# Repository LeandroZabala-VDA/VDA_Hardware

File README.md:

# VDA_Hardware

This repository contains the hardware design files for the **VDA Signal Acquisition System**, a device developed for the non-invasive measurement of **Arterial Diameter Variation (VDA)** using piezoelectric transducers. The system is intended for biomedical research applications and has been validated in both laboratory and clinical environments.

## 📁 Repository Structure

- **/Adquisidor**  
  Contains all design files for the main acquisition board, including schematics, PCB layout, and bill of materials. This board handles signal conditioning, high-resolution analog-to-digital conversion, power regulation, and communication with the PC interface.

- **/frente del gabinete**  
  Includes the PCB designs used as front and rear panels for the device enclosure. These boards support mechanical mounting of connectors, status indicators, and user controls.

## 🛠️ Tools and Compatibility

- Designed using **Autodesk Eagle**  
- Compatible with Eagle version 9.6.2 or later

## ✅ Hardware Status

The version published here is fully functional and has been used in real experimental protocols and patient measurements. It is part of a broader open-source platform that includes firmware and a Python-based user interface.

Key features include:
- Support for a 27 mm piezoelectric transducer
- Fully differential charge amplifier
- Analog bandwidth: 0.16 Hz – 34 Hz
- 16-bit sigma-delta ADC
- 50 Hz digital notch filter
- Electrically isolated sensor interface

## 📂 Included Files

- `.sch` and `.brd` files (schematics and board layout)
- Bill of Materials (`.xls` / `.csv`)
- Reference images of the PCB and assembly
- Enclosure drawings or panel layouts (`.png`, `.step`, etc.)

## 📷 Preview

## 🧩 Related Work

This hardware was developed as part of a final project at the **Laboratorio de Bioingeniería (LABI)**, Universidad Nacional de Mar del Plata (Argentina), and was used in the context of scientific publications, including a peer-reviewed IEEE article.

## 🛡 License

All hardware design files in this repository are licensed under the **CERN Open Hardware License v2 - Strongly Reciprocal (CERN-OHL-S)**.

Any derivative work must also remain open and be shared under the same terms. 

## 📬 Contact

For questions, suggestions or collaboration, feel free to open an issue or contact me.

leandrozabala@mdp.edu.ar

---

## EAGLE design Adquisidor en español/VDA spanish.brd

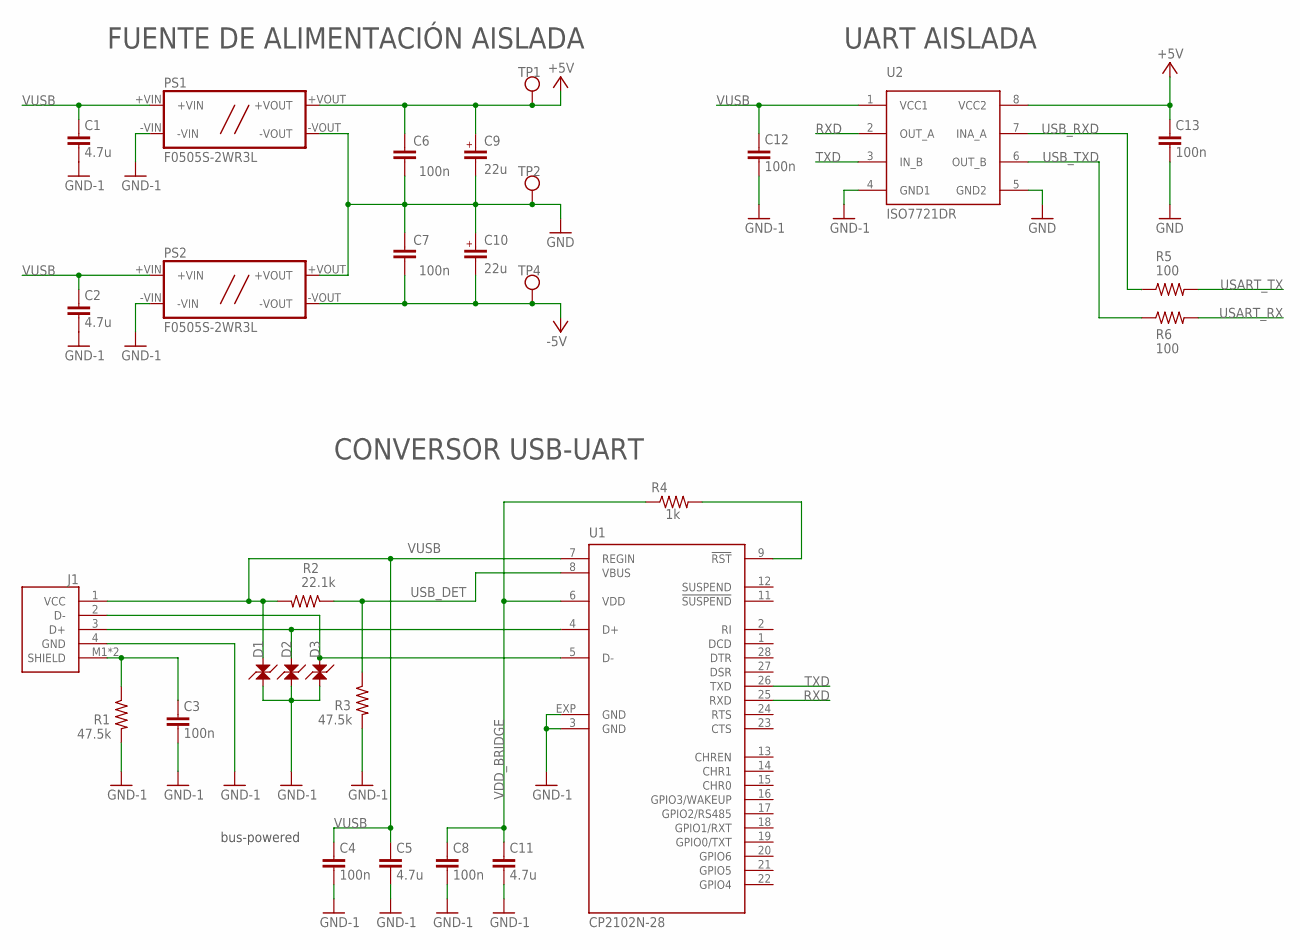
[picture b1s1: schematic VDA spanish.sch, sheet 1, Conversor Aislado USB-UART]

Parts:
C1, C2, C5, C11: 4.7u; C_0805
C3, C4, C6, C7, C8, C12, C13: 100n; C_0603
C9, C10: 22u; CAPAE660X590N
D1, D2, D3: LESD5D5.0CT1G; SOD523
J1: USB-2.0; USB-B
PS1, PS2: F0505S-2WR3L; 0505S-2WR3
R1, R3: 47.5k; R0402
R2: 22.1k; R0402
R4: 1k; R0402
R5, R6: 100; R_0603
TP1, TP2, TP4: HOLE_0.8MM
U1: CP2102N-28; MLP28
U2: ISO7721DR; SO8

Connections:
+5V: C6.P$1 (1), C9.+, C13.P$1 (1), PS1.+VOUT, TP1.1, U2.8 (VCC2); also elsewhere on the board
-5V: C7.P$2 (2), C10.-, PS2.-VOUT, TP4.1; also elsewhere on the board
GND: C6.P$2 (2), C7.P$1 (1), C9.-, C10.+, C13.P$2 (2), PS1.-VOUT, PS2.+VOUT, TP2.1, U2.5 (GND2); also elsewhere on the board
GND-1: C1.P$2 (2), C2.P$2 (2), C3.P$2 (2), C4.P$2 (2), C5.P$2 (2), C8.P$2 (2), C11.P$2 (2), C12.P$2 (2), D1.C, D2.C, D3.C, J1.4 (GND), PS1.-VIN, PS2.-VIN, R1.2, R3.2, U1.3 (GND), U1.EXP (GND), U2.4 (GND1)
unnamed: R4.2, U1.9 (!RST)
RXD: U1.25 (RXD), U2.2 (OUT_A)
SHIELD: C3.P$1 (1), J1.M1 (SHIELD), J1.M2 (SHIELD), R1.1
TXD: U1.26 (TXD), U2.3 (IN_B)
USART_RX: R6.2; also elsewhere on the board
USART_TX: R5.2; also elsewhere on the board
USB_DET: R2.1, R3.1, U1.8 (VBUS)
USB_DN: D3.A, J1.2 (D-), U1.5 (D-)
USB_DP: D2.A, J1.3 (D+), U1.4 (D+)
USB_RXD: R5.1, U2.7 (INA_A)
USB_TXD: R6.1, U2.6 (OUT_B)
VDD_BRIDGE: C8.P$1 (1), C11.P$1 (1), R4.1, U1.6 (VDD)
VUSB: C1.P$1 (1), C2.P$1 (1), C4.P$1 (1), C5.P$1 (1), C12.P$1 (1), D1.A, J1.1 (VCC), PS1.+VIN, PS2.+VIN, R2.2, U1.7 (REGIN), U2.1 (VCC1)

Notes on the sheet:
CONVERSOR USB-UART
bus-powered
FUENTE DE ALIMENTACIÓN AISLADA
UART AISLADA

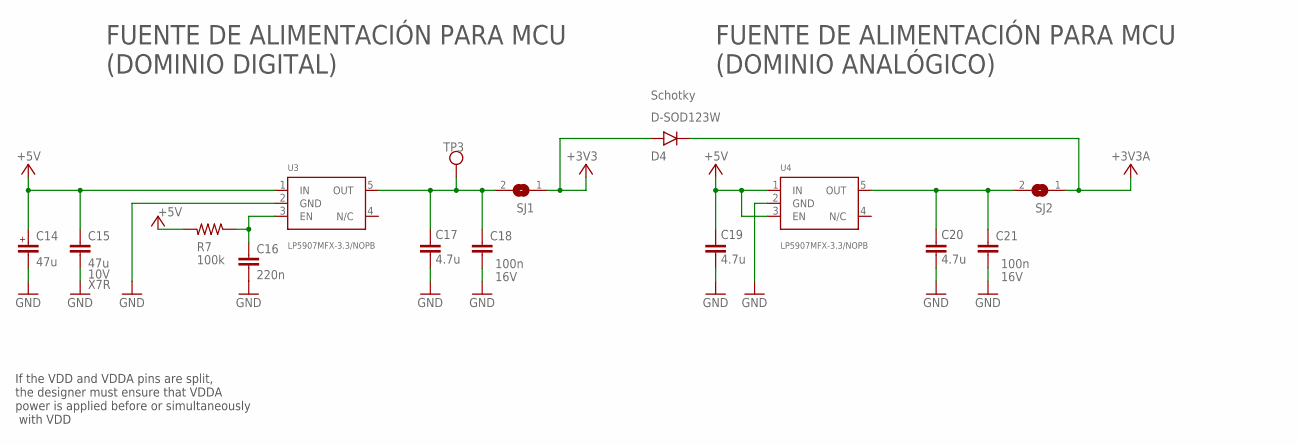
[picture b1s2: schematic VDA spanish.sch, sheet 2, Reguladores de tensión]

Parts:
C14: 47u; A_3216
C15: 47u; C_1206
C16: 220n; C_0603
C17, C19, C20: 4.7u; C_0805
C18, C21: 100n; C_0603
D4: D-SOD123W; SOD123W
R7: 100k; R_0603
SJ1, SJ2: SJ
TP3: HOLE_0.8MM
U3, U4: LP5907MFX-3.3/NOPB; SOT23-5

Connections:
+3V3: D4.A, SJ1.1; also elsewhere on the board
+3V3A: D4.C (K), SJ2.1; also elsewhere on the board
+5V: C14.A (+), C15.P$1 (1), C19.P$1 (1), R7.2, U3.1 (IN), U4.1 (IN), U4.3 (EN); also elsewhere on the board
GND: C14.K (-), C15.P$2 (2), C16.P$2 (2), C17.P$2 (2), C18.P$2 (2), C19.P$2 (2), C20.P$2 (2), C21.P$2 (2), U3.2 (GND), U4.2 (GND); also elsewhere on the board
unnamed: C17.P$1 (1), C18.P$1 (1), SJ1.2, TP3.1, U3.5 (OUT)
unnamed: C16.P$1 (1), R7.1, U3.3 (EN)
unnamed: C20.P$1 (1), C21.P$1 (1), SJ2.2, U4.5 (OUT)

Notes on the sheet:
If the VDD and VDDA pins are split, the designer must ensure that VDDA power is applied before or simultaneously with VDD
FUENTE DE ALIMENTACIÓN PARA MCU (DOMINIO DIGITAL)
FUENTE DE ALIMENTACIÓN PARA MCU (DOMINIO ANALÓGICO)

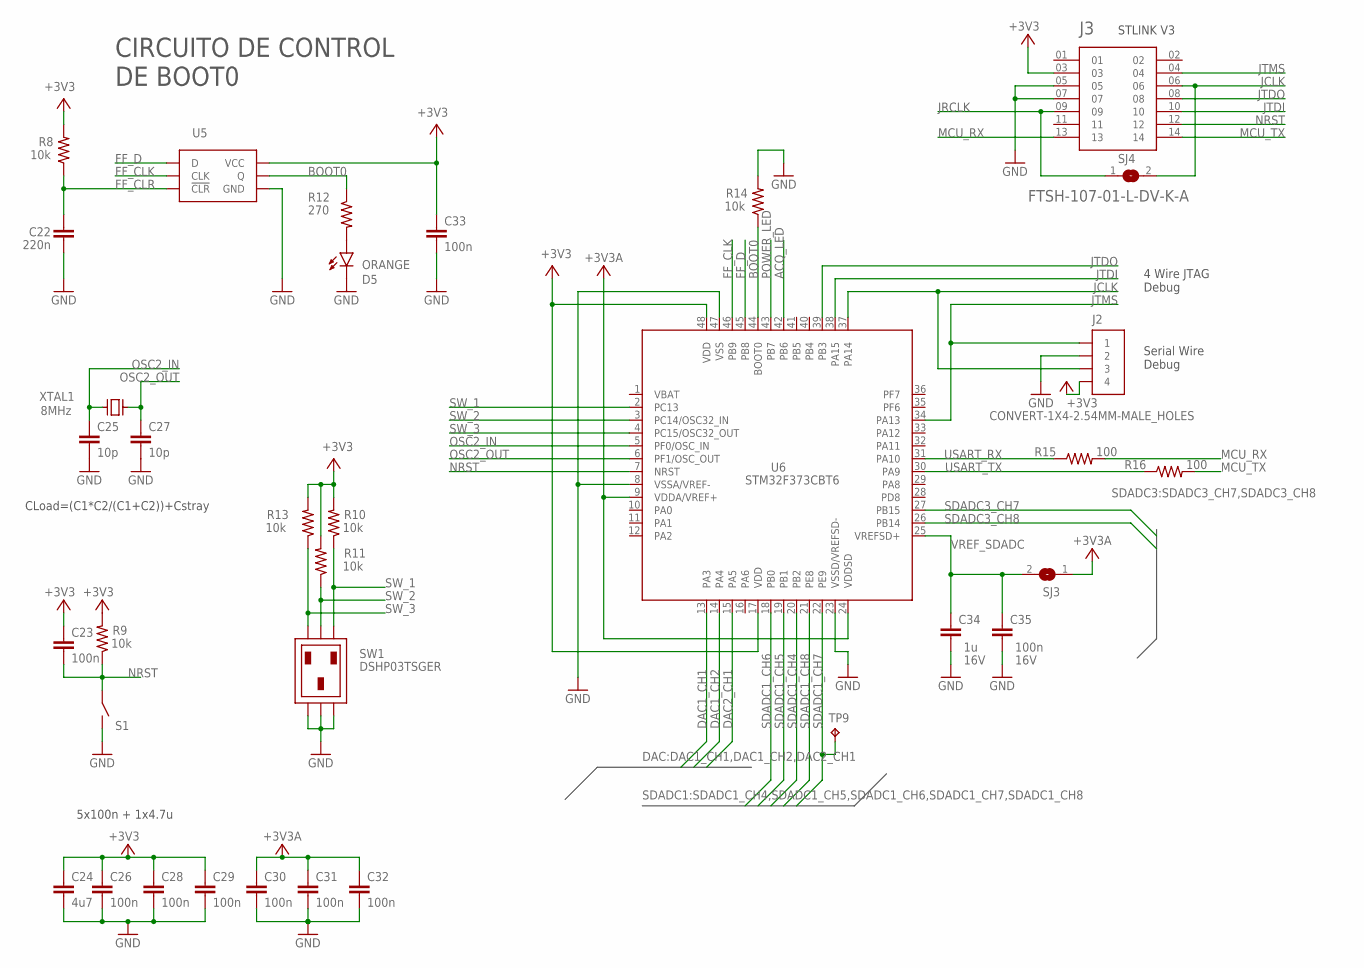
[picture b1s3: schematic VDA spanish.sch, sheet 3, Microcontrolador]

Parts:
C22: 220n; C_0603
C23, C26, C28, C29, C30, C31, C32, C33, C35: 100n; C_0603
C24: 4u7; C_0805
C25, C27: 10p; C_0603
C34: 1u; C_0603
D5: ORANGE; LED_0603_ARROW
J2: CONVERT-1X4-2.54MM-MALE_HOLES; 1X04
J3: FTSH-107-01-L-DV-K-A; SAMTEC_FTSH-107-01-L-DV-K-A
R8, R9, R10, R11, R13, R14: 10k; R_0603
R12: 270; R_0603
R15, R16: 100; R_0603
S1: TSWITCH_SMTR2; SMTR2
SJ3, SJ4: SJ
SW1: DSHP03TSGER; DIPSW-3
TP9: TPTP16R; TP16R
U5: SN74LVC1G175; SOT-23-6
U6: STM32F373CBT6; QFP50P900X900X160-48N
XTAL1: 8MHz; XTAL3.2X2.5; MPN 830108313809

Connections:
+3V3: C23.P$1 (1), C24.P$1 (1), C26.P$1 (1), C28.P$1 (1), C29.P$1 (1), C33.P$1 (1), J2.4, J3.03, R8.2, R9.2, R10.2, R11.2, R13.2, U5.5 (VCC), U6.17 (VDD), U6.48 (VDD); also elsewhere on the board
+3V3A: C30.P$1 (1), C31.P$1 (1), C32.P$1 (1), SJ3.1, U6.9 (VDDA/VREF+), U6.24 (VDDSD); also elsewhere on the board
ACQ_LED: U6.42 (PB6); also elsewhere on the board
BOOT0: R12.1, R14.1, U5.4 (Q), U6.44 (BOOT0); also elsewhere on the board
DAC1_CH1: U6.13 (PA3); also elsewhere on the board
DAC1_CH2: U6.14 (PA4); also elsewhere on the board
DAC2_CH1: U6.15 (PA5); also elsewhere on the board
FF_CLK: U5.1 (CLK), U6.46 (PB9)
FF_CLR: C22.P$1 (1), R8.1, U5.6 (!CLR!)
FF_D: U5.3 (D), U6.45 (PB8)
GND: C22.P$2 (2), C24.P$2 (2), C25.P$2 (2), C26.P$2 (2), C27.P$2 (2), C28.P$2 (2), C29.P$2 (2), C30.P$2 (2), C31.P$2 (2), C32.P$2 (2), C33.P$2 (2), C34.P$2 (2), C35.P$2 (2), D5.K, J2.2, J3.05, J3.07, R14.2, S1.P$3, S1.P$4, SW1.P$2, SW1.P$4, SW1.P$6, U5.2 (GND), U6.8 (VSSA/VREF-), U6.23 (VSSD/VREFSD-), U6.47 (VSS); also elsewhere on the board
JCLK: J2.3, J3.06, SJ4.2, U6.37 (PA14)
JRCLK: J3.09, SJ4.1
JTDI: J3.10, U6.38 (PA15)
JTDO: J3.08, U6.39 (PB3)
JTMS: J2.1, J3.04, U6.34 (PA13)
MCU_RX: J3.13, R15.2
MCU_TX: J3.14, R16.2
unnamed: D5.A, R12.2
NRST: C23.P$2 (2), J3.12, R9.1, S1.P$1, S1.P$2, U6.7 (NRST)
OSC2_IN: C25.P$1 (1), U6.5 (PF0/OSC_IN), XTAL1.P$3 (X2)
OSC2_OUT: C27.P$1 (1), U6.6 (PF1/OSC_OUT), XTAL1.P$1 (X1)
POWER_LED: U6.43 (PB7); also elsewhere on the board
SDADC1_CH4: U6.20 (PB2); also elsewhere on the board
SDADC1_CH5: U6.19 (PB1); also elsewhere on the board
SDADC1_CH6: U6.18 (PB0); also elsewhere on the board
SDADC1_CH7: TP9.TP, U6.22 (PE9)
SDADC1_CH8: U6.21 (PE8); also elsewhere on the board
SDADC3_CH7: U6.27 (PB15); also elsewhere on the board
SDADC3_CH8: U6.26 (PB14); also elsewhere on the board
SW_1: R10.1, SW1.P$1, U6.2 (PC13)
SW_2: R11.1, SW1.P$3, U6.3 (PC14/OSC32_IN)
SW_3: R13.1, SW1.P$5, U6.4 (PC15/OSC32_OUT)
USART_RX: R15.1, U6.31 (PA10); also elsewhere on the board
USART_TX: R16.1, U6.30 (PA9); also elsewhere on the board
VBAT: U6.1 (VBAT)
VREF_SDADC: C34.P$1 (1), C35.P$1 (1), SJ3.2, U6.25 (VREFSD+)

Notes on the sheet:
STLINK V3
5x100n + 1x4.7u
CLoad=(C1*C2/(C1+C2))+Cstray
CIRCUITO DE CONTROL DE BOOT0
Serial Wire Debug
4 Wire JTAG Debug

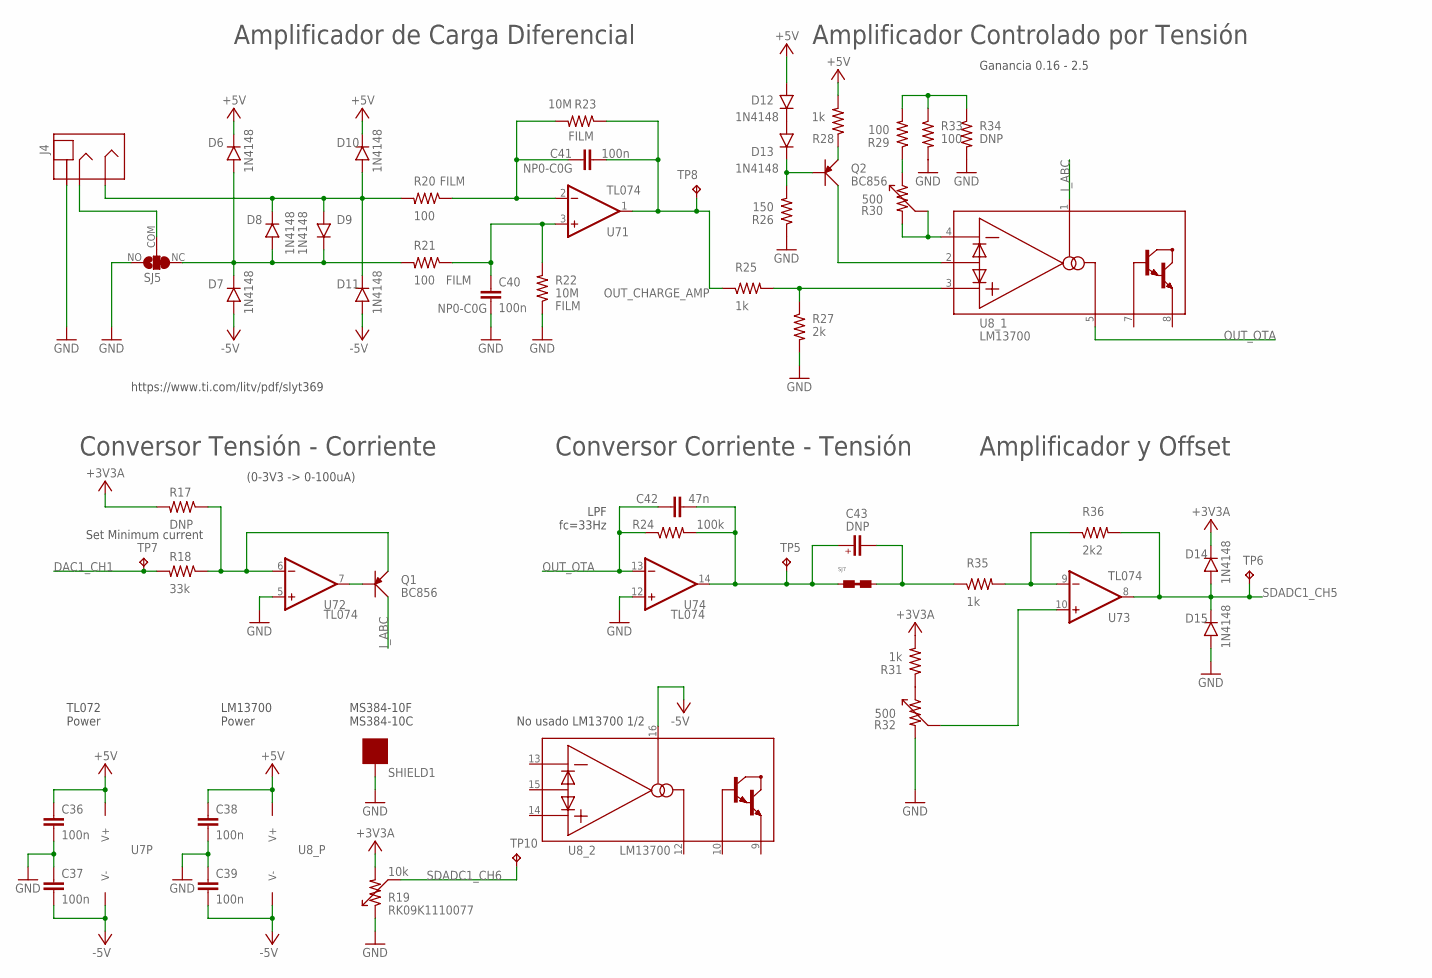
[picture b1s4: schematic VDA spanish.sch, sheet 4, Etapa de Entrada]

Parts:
C36, C37, C38, C39: 100n; C_0603
C40, C41: 100n; C_1206
C42: 47n; C_0603
C43: DNP; CAPAE830X680N
D6, D7, D8, D9, D10, D11, D12, D13, D14, D15: 1N4148; SOD123W
J4: STEREO-JACK; PJ-3200
Q1, Q2: BC856; SOT-23
R17, R34: DNP; R_0603
R18: 33k; R_0603
R19: 10k; POT-09VR1M; MPN RK09K1110077
R20, R21, R29, R33: 100; R_0603
R22, R23: 10M; R_0603
R24: 100k; R_0603
R25, R28, R31, R35: 1k; R_0603
R26: 150; R_0603
R27: 2k; R_0603
R30, R32: 500; RV3.2X4; MPN 3224W-1-501E
R36: 2k2; R_0603
SHIELD1: MS384
SJ5: SJ-PSS; SJ_2S
SJ7: SJUMPER-NC; SJ1
TP5, TP6, TP7, TP8, TP10: TPTP16R; TP16R
U7: TL074; SOIC127P600X175-14N
U8: LM13700; SO16

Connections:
+3V3A: D14.C (K), R17.2, R19.P$3 (2), R31.2; also elsewhere on the board
+5V: C36.P$1 (1), C38.P$1 (1), D6.C (K), D10.C (K), D12.A, R28.2, U7.4 (V+), U8.11 (V+); also elsewhere on the board
-5V: C37.P$2 (2), C39.P$2 (2), D7.A, D11.A, U7.11 (V-), U8.6 (V-), U8.16 (AMP_BIAS); also elsewhere on the board
DAC1_CH1: R18.2, TP7.TP; also elsewhere on the board
GND: C36.P$2 (2), C37.P$1 (1), C38.P$2 (2), C39.P$1 (1), C40.P$2 (2), D15.A, J4.1 (SLEEVE), R19.P$1 (1), R22.1, R26.1, R27.2, R32.3 (2), R33.2, R34.2, SHIELD1.P$1, SHIELD1.P$2, SJ5.NO, U7.5 (+IN), U7.12 (+IN); also elsewhere on the board
I_ABC: Q1.3 (C), U8.1 (AMP_BIAS)
unnamed: C42.P$1 (1), C43.1 (+), R24.2, SJ7.P$1, TP5.TP, U7.14 (OUT)
unnamed: C40.P$1 (1), R21.1, R22.2, U7.3 (+IN)
unnamed: C41.P$1 (1), R20.1, R23.2, U7.2 (-IN)
unnamed: C43.2 (-), R35.1, SJ7.P$2
unnamed: J4.3 (RING), SJ5.COM
unnamed: Q1.2 (E), R17.1, R18.1, U7.6 (-IN)
unnamed: R29.2, R33.1, R34.1
unnamed: Q1.1 (B), U7.7 (OUT)
unnamed: Q2.2 (E), R28.1
unnamed: D12.C (K), D13.A
unnamed: R31.1, R32.1
unnamed: D8.C (K), D9.A, D10.A, D11.C (K), J4.2 (TIP), R20.2
unnamed: D6.A, D7.C (K), D8.A, D9.C (K), R21.2, SJ5.NC
unnamed: R32.2 (C), U7.10 (+IN)
unnamed: R25.2, R27.1, U8.3 (+)
unnamed: R30.2 (C), R30.3 (2), U8.4 (-)
unnamed: Q2.3 (C), U8.2 (D_BIAS)
unnamed: R29.1, R30.1
unnamed: D13.C (K), Q2.1 (B), R26.2
unnamed: R35.2, R36.1, U7.9 (-IN)
OUT_CHARGE_AMP: C41.P$2 (2), R23.1, R25.1, TP8.TP, U7.1 (OUT)
OUT_OTA: C42.P$2 (2), R24.1, U7.13 (-IN), U8.5 (OUT)
SDADC1_CH5: D14.A, D15.C (K), R36.2, TP6.TP, U7.8 (OUT); also elsewhere on the board
SDADC1_CH6: R19.P$2 (C), TP10.TP; also elsewhere on the board

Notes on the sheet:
TL072 Power
LM13700 Power
https://www.ti.com/litv/pdf/slyt369
MS384-10F MS384-10C
Amplificador de Carga Diferencial
Amplificador Controlado por Tensión
Conversor Tensión - Corriente
(0-3V3 -> 0-100uA)
No usado LM13700 1/2
Set Minimum current
Ganancia 0.16 - 2.5
LPF fc=33Hz
Conversor Corriente - Tensión
Amplificador y Offset

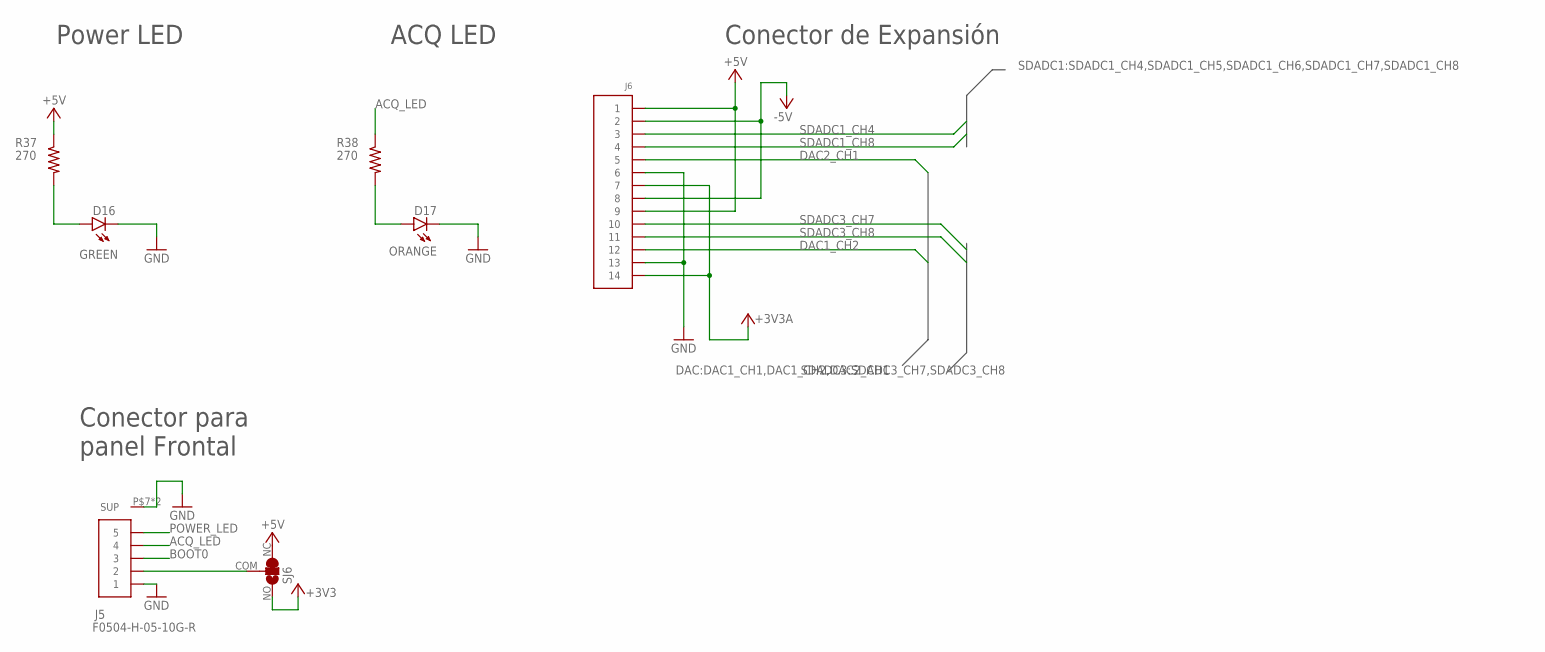
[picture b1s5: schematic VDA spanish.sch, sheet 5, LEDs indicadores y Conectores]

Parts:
D16: GREEN; LED_0603_ARROW
D17: ORANGE; LED_0603_ARROW
J5: F0504-H-05-10G-R
J6: CONVERT-2X7-2.54MM-FEMALE; CONN-VERT-2.54MM-2X7-FEMALE
R37, R38: 270; R_0603
SJ6: SJ-PSS; SJ_2S

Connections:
+3V3: SJ6.NO; also elsewhere on the board
+3V3A: J6.7, J6.14; also elsewhere on the board
+5V: J6.1, J6.9, R37.1, SJ6.NC; also elsewhere on the board
-5V: J6.2, J6.8; also elsewhere on the board
ACQ_LED: J5.P$4 (4), R38.1; also elsewhere on the board
BOOT0: J5.P$3 (3); also elsewhere on the board
DAC1_CH2: J6.12; also elsewhere on the board
DAC2_CH1: J6.5; also elsewhere on the board
GND: D16.K, D17.K, J5.P$1 (1), J5.P$7 (SUP), J5.P$8 (SUP), J6.6, J6.13; also elsewhere on the board
unnamed: D17.A, R38.2
unnamed: D16.A, R37.2
unnamed: J5.P$2 (2), SJ6.COM
POWER_LED: J5.P$5 (5); also elsewhere on the board
SDADC1_CH4: J6.3; also elsewhere on the board
SDADC1_CH8: J6.4; also elsewhere on the board
SDADC3_CH7: J6.10; also elsewhere on the board
SDADC3_CH8: J6.11; also elsewhere on the board

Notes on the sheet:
Power LED
ACQ LED
Conector de Expansión
Conector para panel Frontal

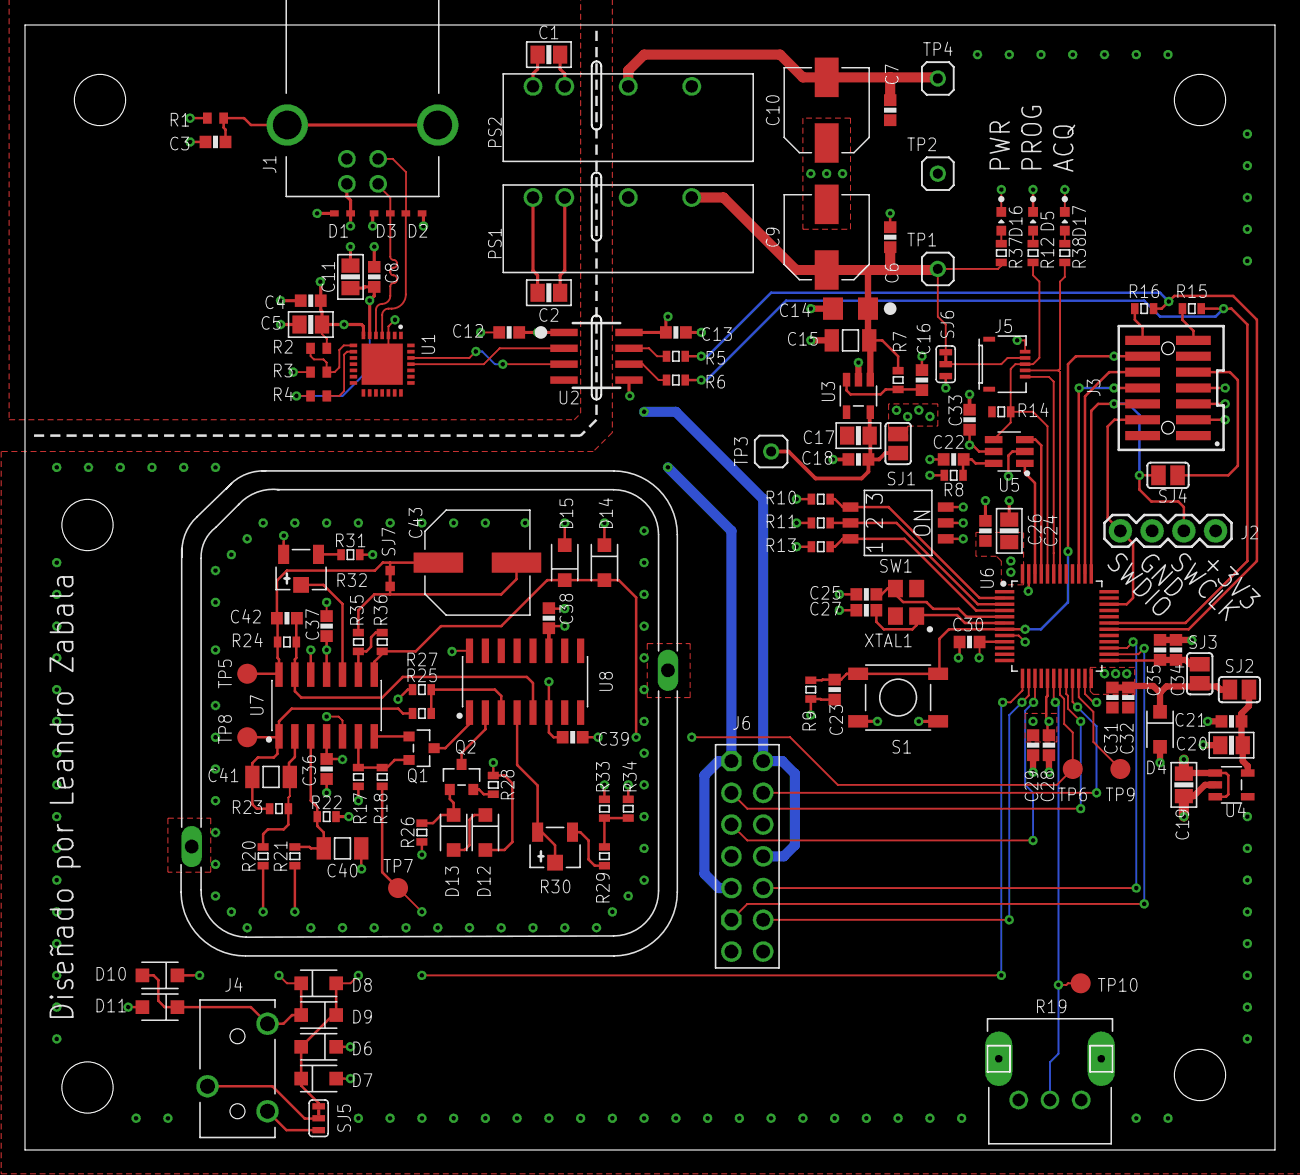
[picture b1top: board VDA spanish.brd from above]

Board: 4 copper layers, 100.0 x 90.0 mm, 137 parts (0 on the bottom side), 79 nets.

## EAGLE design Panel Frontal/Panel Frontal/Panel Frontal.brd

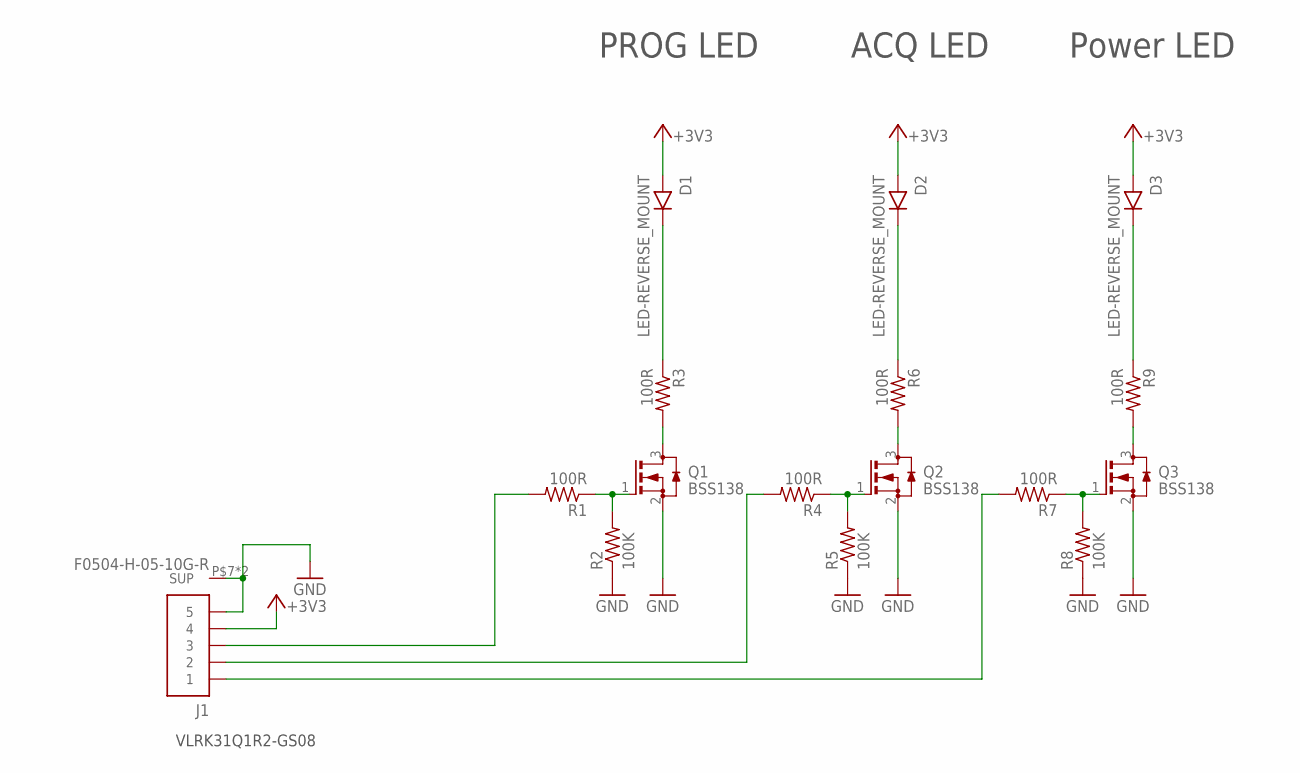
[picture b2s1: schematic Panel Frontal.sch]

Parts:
D1, D2, D3: LED-REVERSE_MOUNT; VLRK31
J1: F0504-H-05-10G-R
Q1, Q2, Q3: BSS138; SOT-23
R1, R3, R4, R6, R7, R9: 100R; R_0603
R2, R5, R8: 100K; R_0603

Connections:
+3V3: D1.A, D2.A, D3.A, J1.P$4 (4)
GND: J1.P$5 (5), J1.P$7 (SUP), J1.P$8 (SUP), Q1.2 (S), Q2.2 (S), Q3.2 (S), R2.1, R5.1, R8.1
unnamed: D2.K, R6.1
unnamed: D1.K, R3.1
unnamed: Q1.1 (G), R1.1, R2.2
unnamed: Q2.1 (G), R4.1, R5.2
unnamed: Q2.3 (D), R6.2
unnamed: Q3.1 (G), R7.1, R8.2
unnamed: J1.P$3 (3), R1.2
unnamed: J1.P$2 (2), R4.2
unnamed: J1.P$1 (1), R7.2
unnamed: Q1.3 (D), R3.2
unnamed: D3.K, R9.1
unnamed: Q3.3 (D), R9.2

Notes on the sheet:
VLRK31Q1R2-GS08
Power LED
ACQ LED
PROG LED

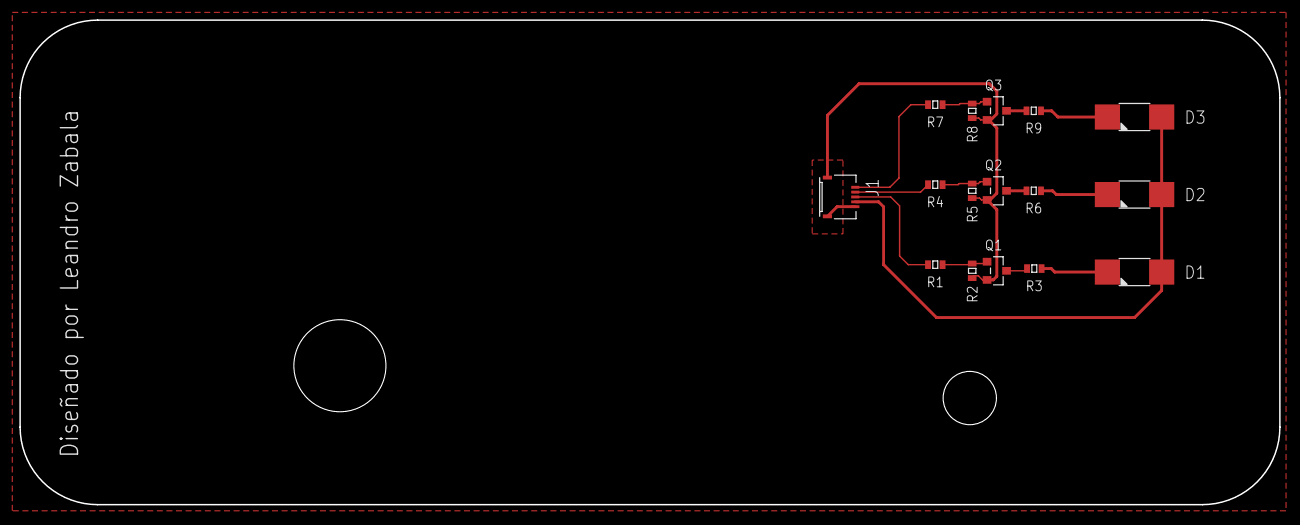
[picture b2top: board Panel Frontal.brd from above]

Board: 2 copper layers, 130.0 x 50.0 mm, 16 parts (0 on the bottom side), 14 nets.

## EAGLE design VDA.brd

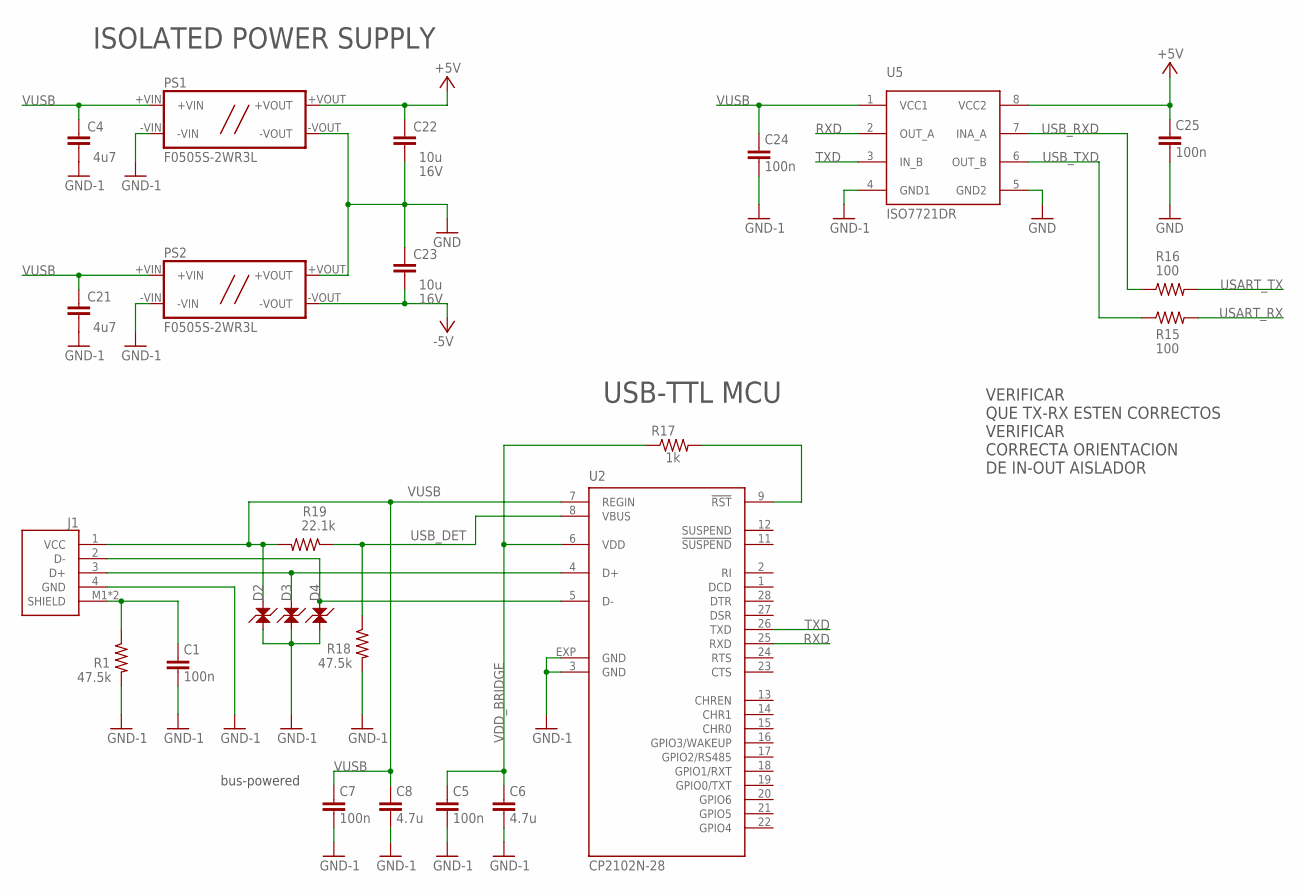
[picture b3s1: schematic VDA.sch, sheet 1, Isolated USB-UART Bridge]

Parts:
C1, C5, C7, C24, C25: 100n; C_0603
C4, C21: 4u7; C_0603
C6, C8: 4.7u; C_0805
C22, C23: 10u; C_0603
D2, D3, D4: LESD5D5.0CT1G; SOD523
J1: USB-2.0; USB-B
PS1, PS2: F0505S-2WR3L; 0505S-2WR3
R1, R18: 47.5k; R0402
R15, R16: 100; R_0603
R17: 1k; R0402
R19: 22.1k; R0402
U2: CP2102N-28; MLP28
U5: ISO7721DR; SO8

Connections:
+5V: C22.P$1 (1), C25.P$1 (1), PS1.+VOUT, U5.8 (VCC2); also elsewhere on the board
-5V: C23.P$2 (2), PS2.-VOUT; also elsewhere on the board
GND: C22.P$2 (2), C23.P$1 (1), C25.P$2 (2), PS1.-VOUT, PS2.+VOUT, U5.5 (GND2); also elsewhere on the board
GND-1: C1.P$2 (2), C4.P$2 (2), C5.P$2 (2), C6.P$2 (2), C7.P$2 (2), C8.P$2 (2), C21.P$2 (2), C24.P$2 (2), D2.C, D3.C, D4.C, J1.4 (GND), PS1.-VIN, PS2.-VIN, R1.2, R18.2, U2.3 (GND), U2.EXP (GND), U5.4 (GND1)
unnamed: R17.2, U2.9 (!RST)
RXD: U2.25 (RXD), U5.2 (OUT_A)
SHIELD: C1.P$1 (1), J1.M1 (SHIELD), J1.M2 (SHIELD), R1.1
TXD: U2.26 (TXD), U5.3 (IN_B)
USART_RX: R15.2; also elsewhere on the board
USART_TX: R16.2; also elsewhere on the board
USB_DET: R18.1, R19.1, U2.8 (VBUS)
USB_DN: D4.A, J1.2 (D-), U2.5 (D-)
USB_DP: D3.A, J1.3 (D+), U2.4 (D+)
USB_RXD: R16.1, U5.7 (INA_A)
USB_TXD: R15.1, U5.6 (OUT_B)
VDD_BRIDGE: C5.P$1 (1), C6.P$1 (1), R17.1, U2.6 (VDD)
VUSB: C4.P$1 (1), C7.P$1 (1), C8.P$1 (1), C21.P$1 (1), C24.P$1 (1), D2.A, J1.1 (VCC), PS1.+VIN, PS2.+VIN, R19.2, U2.7 (REGIN), U5.1 (VCC1)

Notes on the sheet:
USB-TTL MCU
bus-powered
ISOLATED POWER SUPPLY
VERIFICAR QUE TX-RX ESTEN CORRECTOS VERIFICAR CORRECTA ORIENTACION DE IN-OUT AISLADOR

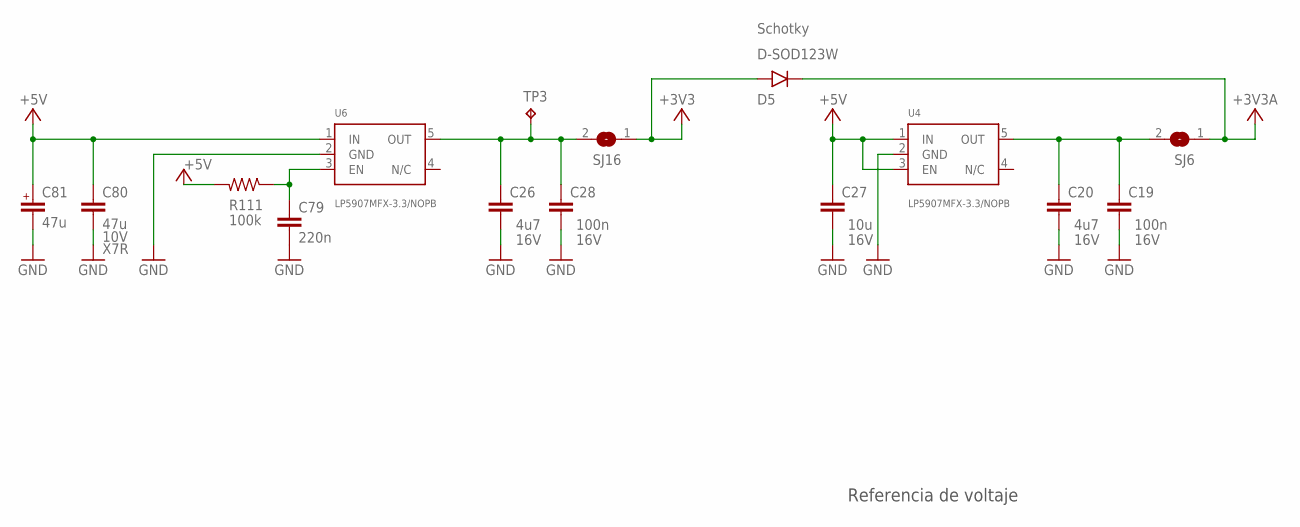
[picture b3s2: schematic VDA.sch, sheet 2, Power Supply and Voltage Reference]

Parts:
C19, C28: 100n; C_0603
C20, C26: 4u7; C_0603
C27: 10u; C_0603
C79: 220n; C_0603
C80: 47u; C_1206
C81: 47u; A_3216
D5: D-SOD123W; SOD123W
R111: 100k; R_0603
SJ6, SJ16: SJ
TP3: TPB1,27; B1,27
U4, U6: LP5907MFX-3.3/NOPB; SOT23-5

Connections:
+3V3: D5.A, SJ16.1; also elsewhere on the board
+3V3A: D5.C (K), SJ6.1; also elsewhere on the board
+5V: C27.P$1 (1), C80.P$1 (1), C81.A (+), R111.2, U4.1 (IN), U4.3 (EN), U6.1 (IN); also elsewhere on the board
GND: C19.P$2 (2), C20.P$2 (2), C26.P$2 (2), C27.P$2 (2), C28.P$2 (2), C79.P$2 (2), C80.P$2 (2), C81.K (-), U4.2 (GND), U6.2 (GND); also elsewhere on the board
unnamed: C26.P$1 (1), C28.P$1 (1), SJ16.2, TP3.TP, U6.5 (OUT)
unnamed: C79.P$1 (1), R111.1, U6.3 (EN)
unnamed: C19.P$1 (1), C20.P$1 (1), SJ6.2, U4.5 (OUT)

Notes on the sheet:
Referencia de voltaje

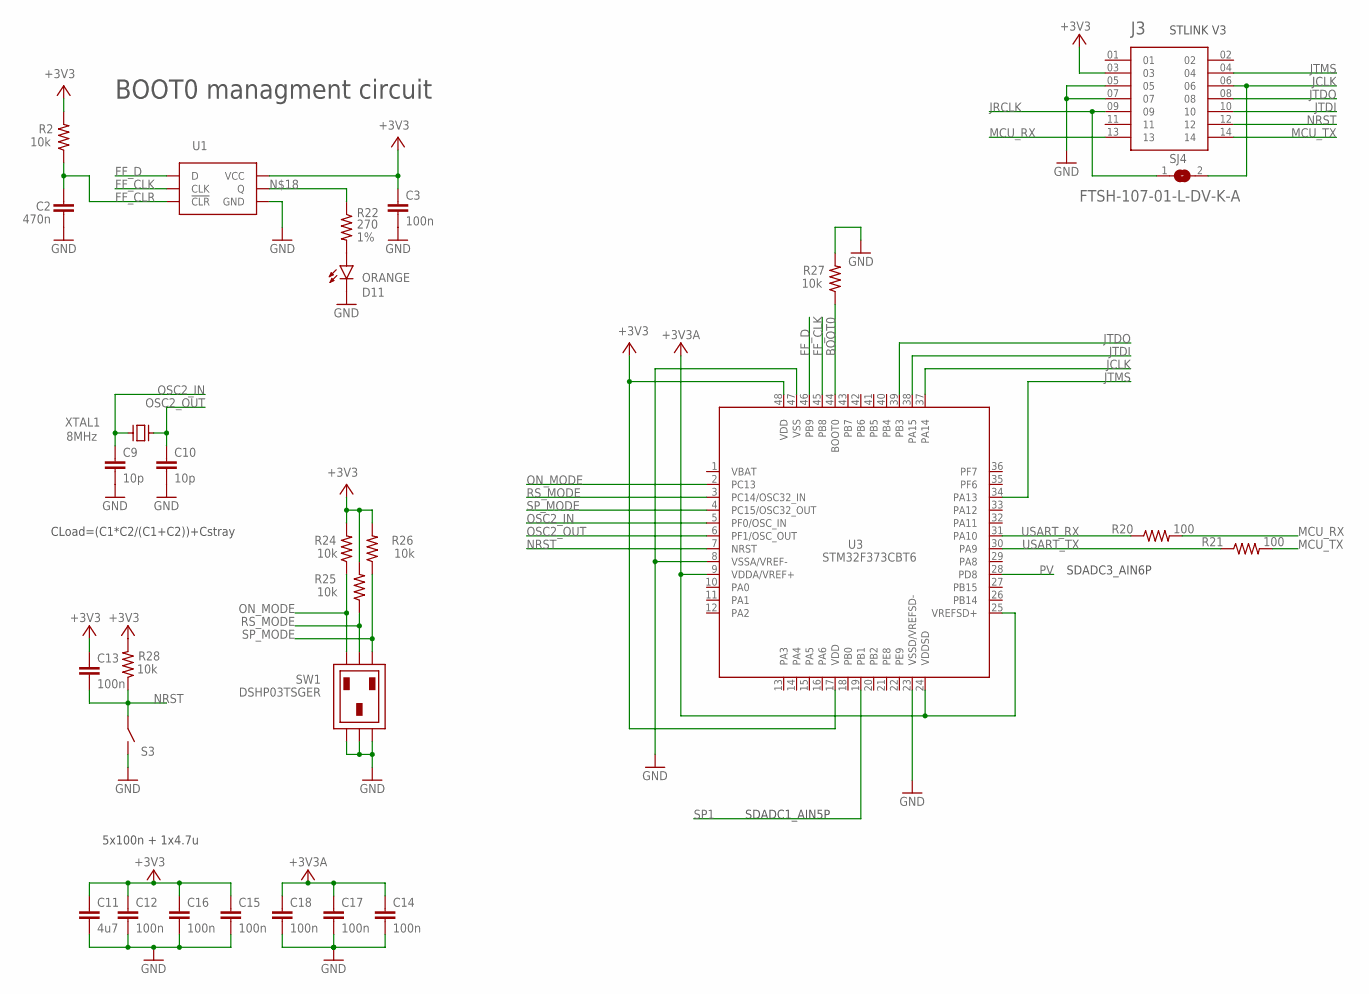
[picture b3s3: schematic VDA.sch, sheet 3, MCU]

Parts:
C2: 470n; C_0603
C3, C12, C13, C14, C15, C16, C17, C18: 100n; C_0603
C9, C10: 10p; C_0603
C11: 4u7; C_0805
D11: ORANGE; LED_0603_ARROW
J3: FTSH-107-01-L-DV-K-A; SAMTEC_FTSH-107-01-L-DV-K-A
R2, R24, R25, R26, R27, R28: 10k; R_0603
R20, R21: 100; R_0603
R22: 270; R_0402
S3: TSWITCH_SMTR2; SMTR2
SJ4: SJ
SW1: DSHP03TSGER; DIPSW-3
U1: SN74LVC1G175; SOT-23-6
U3: STM32F373CBT6; QFP50P900X900X160-48N
XTAL1: 8MHz; XTAL3.2X2.5; MPN 830108313809

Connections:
+3V3: C3.P$1 (1), C11.P$1 (1), C12.P$1 (1), C13.P$1 (1), C15.P$1 (1), C16.P$1 (1), J3.03, R2.2, R24.2, R25.2, R26.2, R28.2, U1.5 (VCC), U3.17 (VDD), U3.48 (VDD); also elsewhere on the board
+3V3A: C14.P$1 (1), C17.P$1 (1), C18.P$1 (1), U3.9 (VDDA/VREF+), U3.24 (VDDSD), U3.25 (VREFSD+); also elsewhere on the board
BOOT0: R27.1, U3.44 (BOOT0)
FF_CLK: U1.1 (CLK), U3.45 (PB8)
FF_CLR: C2.P$1 (1), R2.1, U1.6 (!CLR!)
FF_D: U1.3 (D), U3.46 (PB9)
GND: C2.P$2 (2), C3.P$2 (2), C9.P$2 (2), C10.P$2 (2), C11.P$2 (2), C12.P$2 (2), C14.P$2 (2), C15.P$2 (2), C16.P$2 (2), C17.P$2 (2), C18.P$2 (2), D11.K, J3.05, J3.07, R27.2, S3.P$3, S3.P$4, SW1.P$2, SW1.P$4, SW1.P$6, U1.2 (GND), U3.8 (VSSA/VREF-), U3.23 (VSSD/VREFSD-), U3.47 (VSS); also elsewhere on the board
JCLK: J3.06, SJ4.2, U3.37 (PA14)
JRCLK: J3.09, SJ4.1
JTDI: J3.10, U3.38 (PA15)
JTDO: J3.08, U3.39 (PB3)
JTMS: J3.04, U3.34 (PA13)
MCU_RX: J3.13, R20.2
MCU_TX: J3.14, R21.2
unnamed: D11.A, R22.2
unnamed: R22.1, U1.4 (Q)
NRST: C13.P$2 (2), J3.12, R28.1, S3.P$1, S3.P$2, U3.7 (NRST)
ON_MODE: R24.1, SW1.P$1, U3.2 (PC13)
OSC2_IN: C9.P$1 (1), U3.5 (PF0/OSC_IN), XTAL1.P$3 (X2)
OSC2_OUT: C10.P$1 (1), U3.6 (PF1/OSC_OUT), XTAL1.P$1 (X1)
PV: U3.28 (PD8)
RS_MODE: R25.1, SW1.P$3, U3.3 (PC14/OSC32_IN)
SP1: U3.19 (PB1)
SP_MODE: R26.1, SW1.P$5, U3.4 (PC15/OSC32_OUT)
USART_RX: R20.1, U3.31 (PA10); also elsewhere on the board
USART_TX: R21.1, U3.30 (PA9); also elsewhere on the board
VBAT: U3.1 (VBAT)

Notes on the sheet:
STLINK V3
5x100n + 1x4.7u
SDADC1_AIN5P
SDADC3_AIN6P
CLoad=(C1*C2/(C1+C2))+Cstray
BOOT0 managment circuit
